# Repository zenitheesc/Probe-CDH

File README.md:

# Probe-CDH
<h1 align="center" style="color:white; background-color:black">Probe-CDH</h1>
<h4 align="center"> Telecommunication board for the Zenith's Stack architecture.</h4>

<p align="center">

</p>

<p align="center">
    <a href="#environment-and-tools">Environment and Tools</a> •
    <a href="#Z-Hub">Z-Hub</a> •
    <a href="#Block-Diagram">Block Diagram</a> •
    <a href="#Schematic">Schematic</a> • 
    <a href="#Board">Board</a>
</p>

## Environment and tools

This board was designed using KiCad 5.1.10.

## Block Diagram

## Z-Hub

This board contains a Stack Connector, with the 2021 Z-Hub pinout.

<table align = "center">
  <thead>
    <tr>
      <th colspan=2>   Z-Hub 2021   </th>
    </tr>
  </thead>
  <tbody>
    <tr>
      <td>GND</td>
      <td>GND</td>
    </tr>
    <tr>
      <td>GND</td>
      <td>GND</td>
    </tr>
    <tr>
      <td>BAT+</td>
      <td>BAT+</td>
    </tr>
    <tr>
      <td>SOl+</td>
      <td>SOl-</td>
    </tr>
    <tr>
      <td>5V</td>
      <td>5V</td>
    </tr>
    <tr>
      <td>3V3</td>
      <td>3V3</td>
    </tr>
    <tr>
      <td>MISO1</td>
      <td>MOSI1</td>
    </tr>
    <tr>
      <td>SCK1</td>
      <td>CAN_H</td>
    </tr>
    <tr>
      <td>SDA </td>
      <td>CAN_L</td>
    </tr>
    <tr>
      <td>SCL</td>
      <td>CE02</td>
    </tr>
    <tr>
      <td>CE11</td>
      <td>CE12</td>
    </tr>
    <tr>
      <td>SDA1</td>
      <td>SCL1</td>
    </tr>
    <tr>
      <td>SDA2</td>
      <td>SCL2</td>
    </tr>
    <tr>
      <td>TX1</td>
      <td>RX1</td>
    </tr>
    <tr>
      <td>TX2</td>
      <td>RX2</td>
    </tr>
    <tr>
      <td>DIG1</td>
      <td>DIG6</td>
    </tr>
    <tr>
      <td>ALRT1</td>
      <td>/CHRG</td>
    </tr>
    <tr>
      <td>PWM</td>
      <td>DIG8</td>
    </tr>
    <tr>
      <td>/FAULT</td>
      <td>DIG9</td>
    </tr>
    <tr>
      <td>DIG5</td>
      <td>DIG10</td>
    </tr>
  </tbody>
</table>

## Schematic

The design was separated in hierarchical sheets to accommodate all components in an orderly way.

The first page contains the STM32L476 with all its accompanying circuits; crystals, debugging LED, Boot solder jumper, decoupling capacitors and reset buttons. On the same page you find the stack connector along with a programming and debugging connector and an external GPS connector (can also be used for UART communication with external devices, it’s bad but it’s there).

The second page contains the two LoRa and (G)FSK radios, one capable of 2 W off transmission power when fed with 6 V (obtained with the linear regulator), and the other capable of 160 mW, used as a backup or low power option. Both of them are based on the Semtech SX1262 transceiver, for operation at 915 MHz. The u-blox NEO-M8N also lives on this page, with its backup super capacitor for hot starts.

The last page houses the remaining peripherals which include the SD Card, the 128 Mb Flash, the CAN Transceiver and the buzzer connector with its mosfet, which may also be used as an external actuator with a max current of 1 A (the mosfet actually handles up to 1,5 A but let’s not push it too far).  

## Board

---

<p align="center">

</p>
<p align = "center">
<a href="zenith.eesc@gmail.com">zenith.eesc@gmail.com</a>
</p>

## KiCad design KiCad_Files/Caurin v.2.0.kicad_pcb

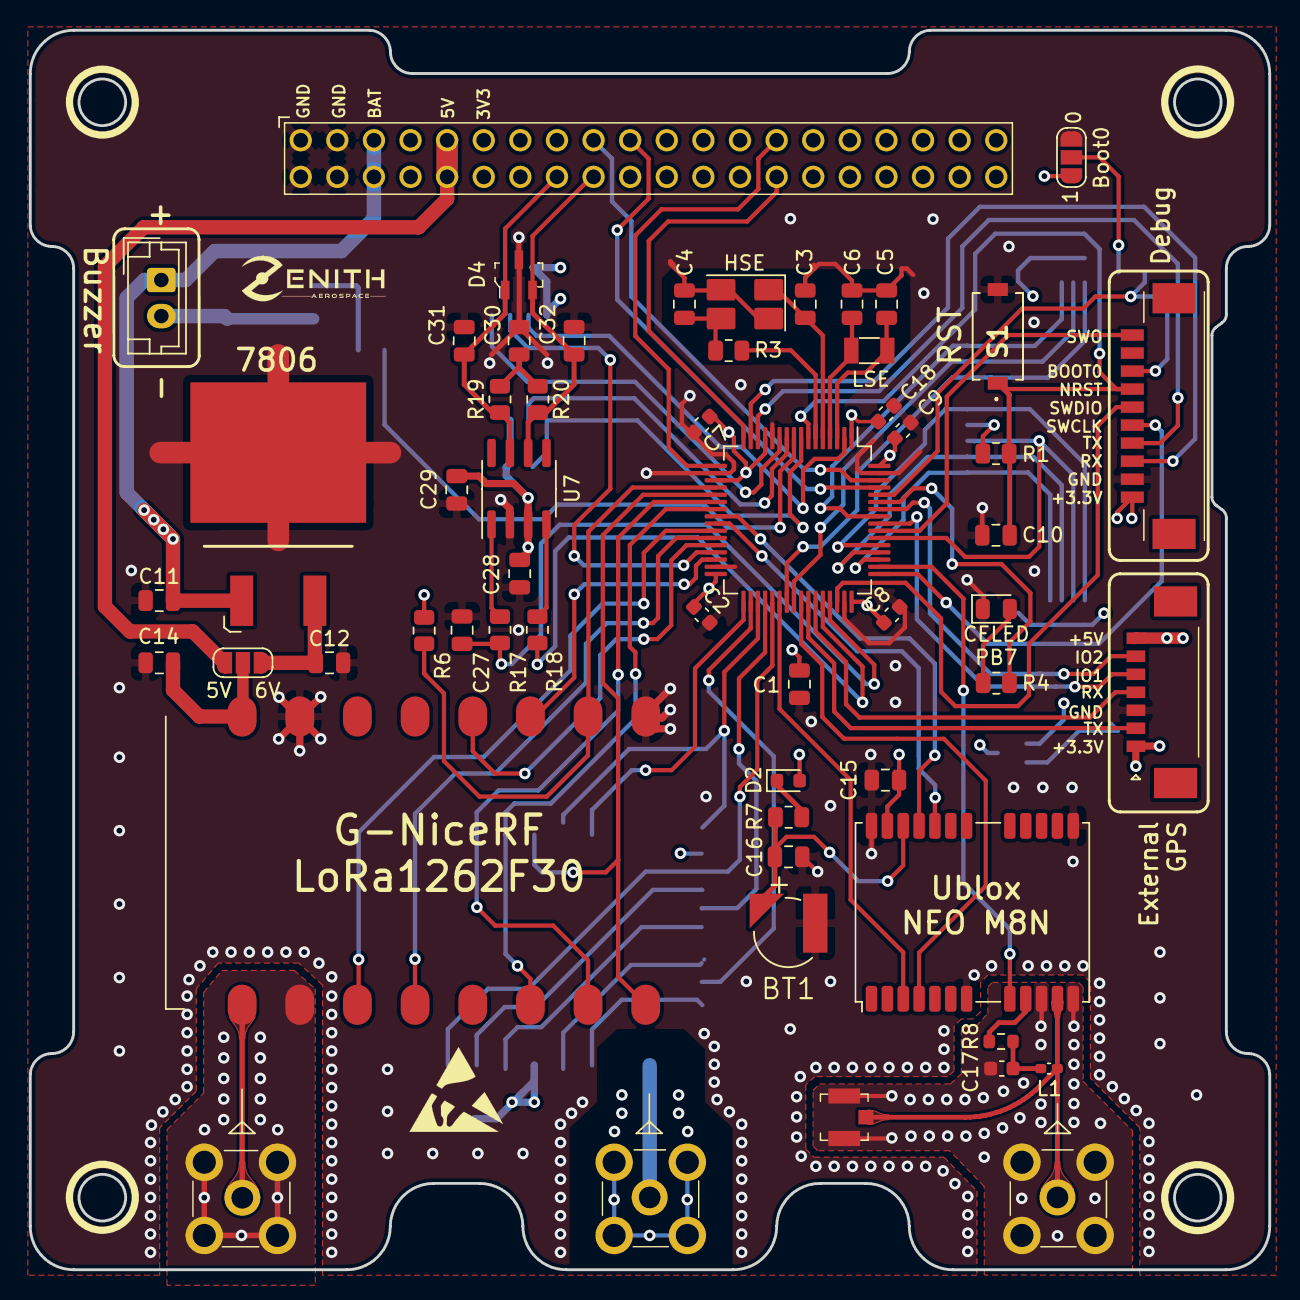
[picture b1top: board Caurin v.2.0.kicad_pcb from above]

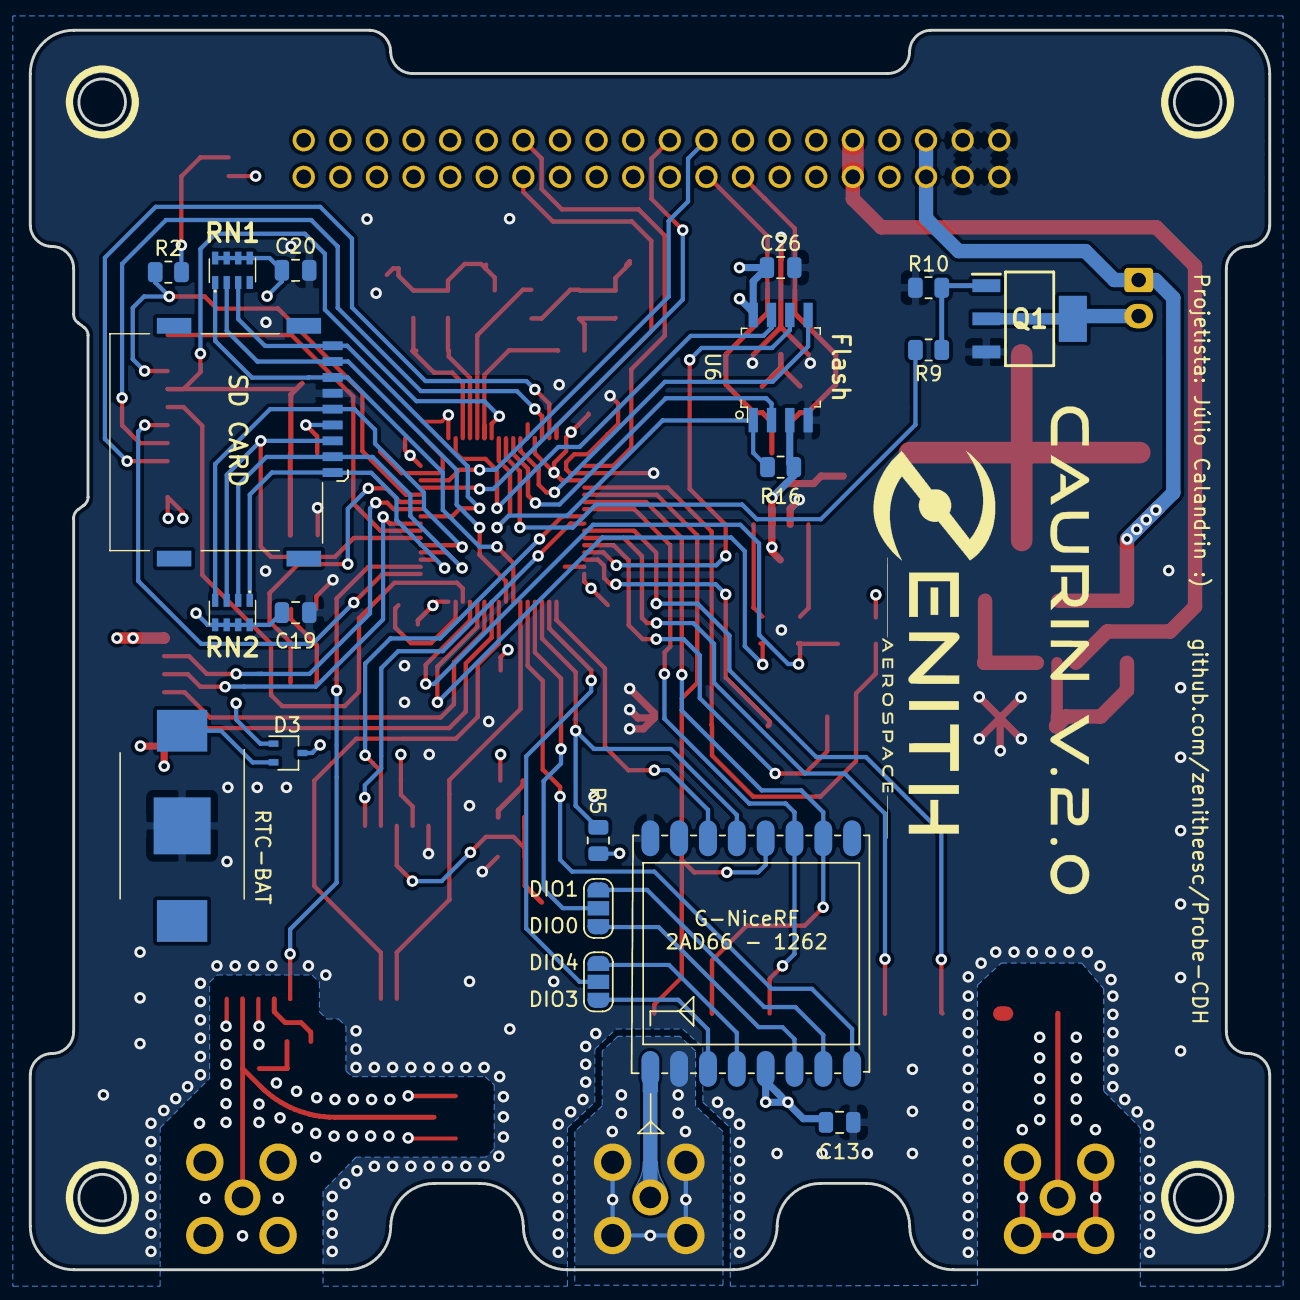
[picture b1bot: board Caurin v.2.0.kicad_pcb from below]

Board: 4 copper layers, 86.0 x 86.0 mm, 75 parts (19 on the bottom side), 85 nets.

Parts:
16M1: Crystal_GND24; Crystal_SMD_5032-4Pin_5.0x3.2mm_Hand_Soldering
BT1: ML414H_IV01E; SEIKO_ML414H_IV01E
BT2: Battery_Cell; 3030
C1, C20, C29: 4.7u; C_0805_2012Metric
C2, C7, C8, C9, C18: 100n; C_0603_1608Metric
C3, C4: 24p; C_0805_2012Metric
C5, C6: 7p; C_0805_2012Metric
C10: 1u; C_0805_2012Metric
C11: 330n; C_0805_2012Metric
C12, C19, C26, C28: 100n; C_0805_2012Metric
C13, C14, C15, C16: 1uF; C_0805_2012Metric
C17: 10nF; C_0603_1608Metric
C27, C31, C32: 33p; C_0805_2012Metric
C30: 4.7n; C_0805_2012Metric
D1: LED; LED_0805_2012Metric
D2: D_Schottky_Small; D_0603_1608Metric
D3: BAT54CW; SOT-323_SC-70
D4: PESD2CANFD27L-UX; SOT-23-3
IC1: L7806ABD2T-TR; ST_D2PAK
J1: ESQ-120-39-G-D; ESQ-120-Y-X-D
J2: Conn_01x12_Male; 532611071
J3: Conn_01x09_Male; 533980771
J4, J5, J7: CONSMA001-SMD-G; RF_SMA_Vertical_5-1814832-1
J6: U_FL-R-SMT_10_; Coax_Conn_U.FL
J8: MEM2075-00-140-01-A; MEM20750014001A
J9: Conn_01x02_Male; JST_EH_B2B-EH-A_1x02_P2.50mm_Vertical
JP1, JP2, JP3, JP4: SolderJumper_3_Open; SolderJumper-3_P1.3mm_Open_RoundedPad1.0x1.5mm_NumberLabels
L1: L_Small; L_0402_1005Metric_Pad0.77x0.64mm_HandSolder
Q1: PMT280ENEAX; SOT230P700X180-4N
R1, R2, R10, R16: 10k; R_0805_2012Metric
R3: 390; R_0805_2012Metric
R4, R17, R18: 1k; R_0805_2012Metric
R5, R6: 10K; R_0805_2012Metric
R7: 3.3K; R_0805_2012Metric
R8: 10; R_0603_1608Metric
R9: 330; R_0805_2012Metric
R19, R20: 60; R_0805_2012Metric
RN1, RN2: R_Pack_47k; YC164JR07220RL
S1: PTS636_SM43J_SMTR_LFS; PTS636SM43JSMTRLFS
U1: STM32L476RGTx; LQFP-64_10x10mm_P0.5mm
U2: 2AD66-1262; 2AD66-126x
U3: LoRa1262F30
U5: NEO-M8N; ublox_NEO
U6: W25Q32JVSSIQ_TR; SOIC-8_W5.6mm
U7: TCAN330G; SOIC-8_3.9x4.9mm_P1.27mm
Y1: 32,768k; Crystal_SMD_3215-2Pin_3.2x1.5mm

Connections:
3V3: C1.1, C2.1, C7.1, C8.1, C9.1, C13.1, C15.1, C19.1, C20.1, C26.1, C28.1, C29.1, D2.2, D3.1, J1.11, J1.12, J2.1, J3.1, J8.P4, JP1.3, R1.1, R5.2, R6.2, R16.2, RN1.5, RN1.6, RN1.7, RN1.8, RN2.5, RN2.6, RN2.7, RN2.8, U1.13, U1.19, U1.32, U1.48, U1.64, U2.13, U5.23, U6.3, U6.8, U7.3
5V: J1.9, J1.10, J3.7, JP2.3
BAT+: C11.2, IC1.1, J1.5, J1.6, J9.1
BOOT0: J2.8, R2.1, U1.60
BUS_RX1: J1.28, U1.16
BUS_SCL1: J1.19, U1.61
BUS_SDA1: J1.17, U1.62
BUS_TX1: J1.27, U1.17
CAN_H: C31.2, D4.1, J1.16, R19.1, U7.7
CAN_L: C32.2, D4.2, J1.18, R20.2, U7.6
CAN_RX: R18.2, U1.44
CAN_TX: C27.2, R17.2, U1.45
DEBUG_LED: R4.1, U1.59
EXT_BUZZER: R9.2, U1.9
EXT_GPS_GPIO1: J3.6, U1.58
EXT_GPS_GPIO2: J3.5, U1.56
EXT_GPS_RX: J3.4, U1.43
EXT_GPS_TX: J3.2, U1.42
FLASH_NRST: U1.2, U6.7
FLASH_NSS: R16.1, U1.8, U6.1
FLASH_SPI_CLK: U1.29, U6.6
FLASH_SPI_MISO: U1.10, U6.2
FLASH_SPI_MOSI: U1.11, U6.5
GND: 16M1.2, 16M1.4, BT1.2, BT2.2, C1.2, C2.2, C3.2, C4.1, C5.2, C6.1, C7.2, C8.2, C9.2, C10.2, C11.1, C12.2, C13.2, C14.2, C15.2, C16.2, C18.2, C19.2, C20.2, C26.2, C27.1, C28.2, C29.2, C30.1, C31.1, C32.1, D1.1, D4.3, IC1.3, J1.1, J1.2, J1.3, J1.4, J2.2, J3.3, J8.P6, JP1.1, Q1.3, R10.1, S1.2, U1.12, U1.18, U1.31, U1.47, U1.63, U2.8, U3.2, U3.8, U5.7, U5.13, U5.24, U6.4, U7.2
GNDA: C17.2, J6.1, J7.1, U5.10, U5.12
GPS_EXTINT: U1.41, U5.4
GPS_RESET: U1.50, U5.8
GPS_RX: U1.24, U5.21
GPS_TIMEPULSE: U1.38, U5.3
GPS_TX: U1.25, U5.20
HSE_IN: 16M1.1, C3.1, U1.5
HSE_OUT: R3.1, U1.6
LSE_IN: C5.1, U1.3, Y1.2
LSE_OUT: C6.2, U1.4, Y1.1
NRST: C10.1, J2.7, R1.2, S1.1, U1.7
unnamed: 16M1.3, C4.2, R3.2
unnamed: BT1.1, C16.1, R7.1, U5.22
unnamed: BT2.1, D3.2
unnamed: C12.1, IC1.2, JP2.1
unnamed: C14.1, JP2.2, U3.1
unnamed: C17.1, L1.1, R8.1
unnamed: C30.2, R19.2, R20.1
unnamed: D1.2, R4.2
unnamed: D2.1, R7.2
unnamed: J4.1, U2.10
unnamed: J4.2, U2.9
unnamed: J5.1, U3.15
unnamed: J5.2, U3.16
unnamed: J6.2, J7.2, L1.2, U5.11
unnamed: J9.2, Q1.2, Q1.4
unnamed: JP1.2, R2.2
unnamed: JP3.1, U2.14
unnamed: JP3.3, U2.15
unnamed: JP4.1, U2.11
unnamed: JP4.3, U2.12
unnamed: Q1.1, R9.1, R10.2
unnamed: R8.2, U5.9
unnamed: R17.1, U7.1
unnamed: R18.1, U7.4
RADIO1_BUSY: U1.30, U3.6
RADIO1_DIO1: U1.27, U3.13
RADIO1_DIO3: U1.26, U3.14
RADIO1_NRST: U1.28, U3.5
RADIO1_NSS: R6.1, U1.20, U3.7
RADIO2_BUSY: U1.37, U2.16
RADIO2_DIO1: JP3.2, U1.36
RADIO2_DIO3: JP4.2, U1.34
RADIO2_NRST: U1.33, U2.6
RADIO2_NSS: R5.1, U1.35, U2.5
RTC_BAT: C18.1, D3.3, U1.1
SD_CARD_CD: J8.P9, RN1.3, U1.57
SD_CARD_CLK: J8.P5, RN2.4, U1.53
SD_CARD_CMD: J8.P3, RN2.3, U1.54
SD_CARD_DAT0: J8.P7, RN1.1, U1.39
SD_CARD_DAT1: J8.P8, RN1.2, U1.40
SD_CARD_DAT2: J8.P1, RN2.1, U1.51
SD_CARD_DAT3: J8.P2, RN2.2, U1.52
SPI1_MISO: U1.22, U2.2, U3.10
SPI1_MOSI: U1.23, U2.3, U3.11
SPI1_SCK: U1.21, U2.4, U3.9
SWCLK: J2.5, U1.49
SWDIO: J2.6, U1.46
SWO: J2.10, U1.55
UART_RX: J2.3, U1.15
UART_TX: J2.4, U1.14

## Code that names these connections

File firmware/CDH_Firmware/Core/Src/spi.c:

/* USER CODE BEGIN Header */
/**
  ******************************************************************************
  * @file    spi.c
  * @brief   This file provides code for the configuration
  *          of the SPI instances.
  ******************************************************************************
  * @attention
  *
  * Copyright (c) 2022 STMicroelectronics.
  * All rights reserved.
  *
  * This software is licensed under terms that can be found in the LICENSE file
  * in the root directory of this software component.
  * If no LICENSE file comes with this software, it is provided AS-IS.
  *
  ******************************************************************************
  */
/* USER CODE END Header */
/* Includes ------------------------------------------------------------------*/
#include "spi.h"

/* USER CODE BEGIN 0 */

/* USER CODE END 0 */

SPI_HandleTypeDef hspi1;

/* SPI1 init function */
void MX_SPI1_Init(void)
{

  /* USER CODE BEGIN SPI1_Init 0 */

  /* USER CODE END SPI1_Init 0 */

  /* USER CODE BEGIN SPI1_Init 1 */

  /* USER CODE END SPI1_Init 1 */
  hspi1.Instance = SPI1;
  hspi1.Init.Mode = SPI_MODE_MASTER;
  hspi1.Init.Direction = SPI_DIRECTION_2LINES;
  hspi1.Init.DataSize = SPI_DATASIZE_4BIT;
  hspi1.Init.CLKPolarity = SPI_POLARITY_LOW;
  hspi1.Init.CLKPhase = SPI_PHASE_1EDGE;
  hspi1.Init.NSS = SPI_NSS_SOFT;
  hspi1.Init.BaudRatePrescaler = SPI_BAUDRATEPRESCALER_8;
  hspi1.Init.FirstBit = SPI_FIRSTBIT_MSB;
  hspi1.Init.TIMode = SPI_TIMODE_DISABLE;
  hspi1.Init.CRCCalculation = SPI_CRCCALCULATION_DISABLE;
  hspi1.Init.CRCPolynomial = 7;
  hspi1.Init.CRCLength = SPI_CRC_LENGTH_DATASIZE;
  hspi1.Init.NSSPMode = SPI_NSS_PULSE_ENABLE;
  if (HAL_SPI_Init(&hspi1) != HAL_OK)
  {
    Error_Handler();
  }
  /* USER CODE BEGIN SPI1_Init 2 */

  /* USER CODE END SPI1_Init 2 */

}

void HAL_SPI_MspInit(SPI_HandleTypeDef* spiHandle)
{

  GPIO_InitTypeDef GPIO_InitStruct = {0};
  if(spiHandle->Instance==SPI1)
  {
  /* USER CODE BEGIN SPI1_MspInit 0 */

  /* USER CODE END SPI1_MspInit 0 */
    /* SPI1 clock enable */
    __HAL_RCC_SPI1_CLK_ENABLE();

    __HAL_RCC_GPIOA_CLK_ENABLE();
    /**SPI1 GPIO Configuration
    PA5     ------> SPI1_SCK
    PA6     ------> SPI1_MISO
    PA7     ------> SPI1_MOSI
    */
    GPIO_InitStruct.Pin = GPIO_PIN_5|GPIO_PIN_6|GPIO_PIN_7;
    GPIO_InitStruct.Mode = GPIO_MODE_AF_PP;
    GPIO_InitStruct.Pull = GPIO_NOPULL;
    GPIO_InitStruct.Speed = GPIO_SPEED_FREQ_VERY_HIGH;
    GPIO_InitStruct.Alternate = GPIO_AF5_SPI1;
    HAL_GPIO_Init(GPIOA, &GPIO_InitStruct);

  /* USER CODE BEGIN SPI1_MspInit 1 */

  /* USER CODE END SPI1_MspInit 1 */
  }
}

void HAL_SPI_MspDeInit(SPI_HandleTypeDef* spiHandle)
{

  if(spiHandle->Instance==SPI1)
  {
  /* USER CODE BEGIN SPI1_MspDeInit 0 */

  /* USER CODE END SPI1_MspDeInit 0 */
    /* Peripheral clock disable */
    __HAL_RCC_SPI1_CLK_DISABLE();

    /**SPI1 GPIO Configuration
    PA5     ------> SPI1_SCK
    PA6     ------> SPI1_MISO
    PA7     ------> SPI1_MOSI
    */
    HAL_GPIO_DeInit(GPIOA, GPIO_PIN_5|GPIO_PIN_6|GPIO_PIN_7);

  /* USER CODE BEGIN SPI1_MspDeInit 1 */

  /* USER CODE END SPI1_MspDeInit 1 */
  }
}

/* USER CODE BEGIN 1 */

/* USER CODE END 1 */

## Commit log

2022-01-18 Add the actual board.
2022-01-19 Update 7806 Traces
2022-01-20 Add shapes3D folder
    Now all 3D models for the components are stored in a single folder, thanks to the Archive Plugin from https://github.com/MitjaNemec/Kicad_action_plugins.git
2022-01-28 Gerado projeto da CubeIDE
2022-02-04 Add RTC backup battery
    Add the CR1025 RTC Button Cell Battery. Update schematic images and PDF.
2022-02-05 Update RTC Battery silk screen name
2022-03-01 Modified code generation settings for architecture
2022-03-01 Added Architecture files of CDH
2022-03-08 Corrigido bug de não enviar todos os pacotes
2022-03-08 Corrigido O BUG de pacotes perdidos da OBSAT
2022-05-24 Bug Fix
    -Scientific notation (float)
    -Optimize fwrite() in FLASH
    -Remove format from fopen()
    -Fix filename buffer
    -Add static function create_template
2022-07-14 Add solder jumper for DIO pins.
    Adds solder jumper for DIO pin compatibility between SX1276 and SX1262 low power radios.
    Also added the name of the designer (me).
2023-02-08 Update fp-info-cache
